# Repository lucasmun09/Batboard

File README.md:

# Batboard
Sonar amplification board to be used in conjunction with Arduino Due

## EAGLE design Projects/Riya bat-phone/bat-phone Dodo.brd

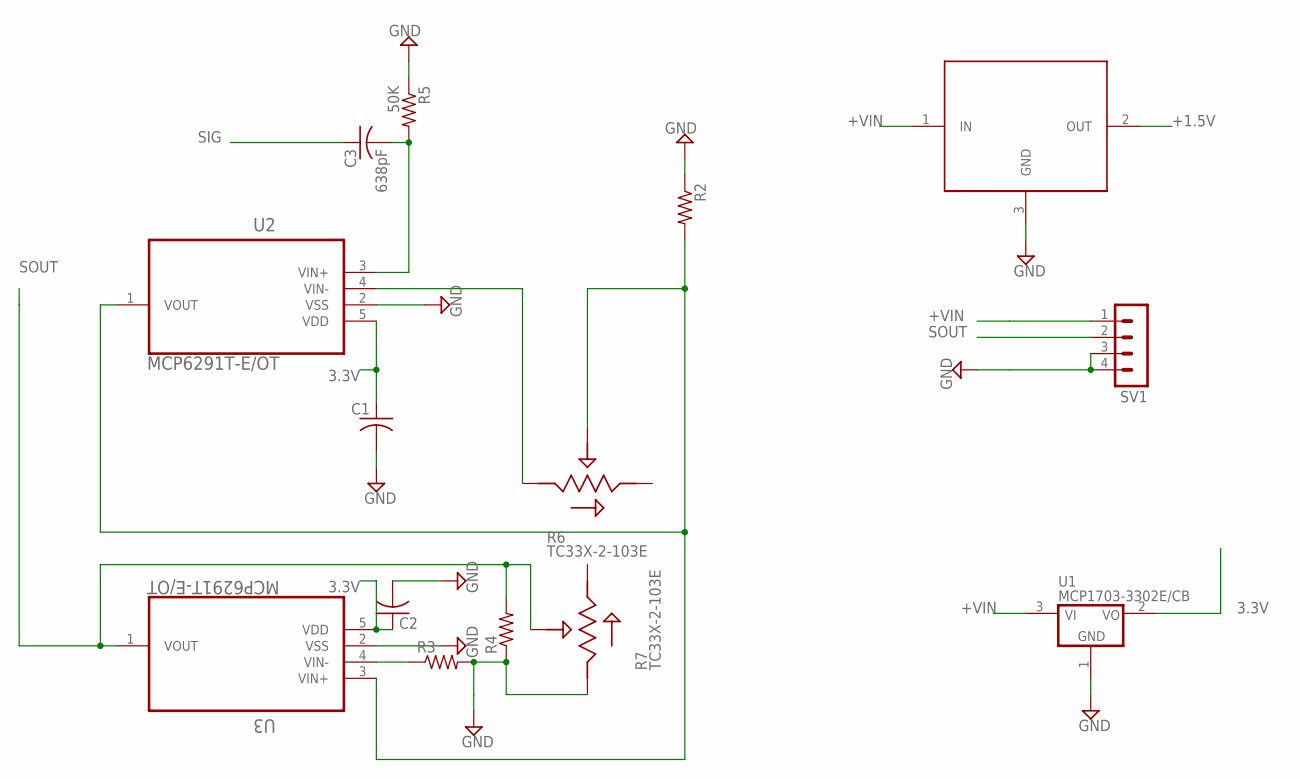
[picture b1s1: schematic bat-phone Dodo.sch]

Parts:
C1, C2: C-USC0603K; C0603K
C3: 638pF; C0603K
R2, R3, R4: R-US_R0603; R0603
R5: 50K; R0603
R6, R7: TC33X-2-103E; 35WR
SV1: MA04-1
U1: MCP1703-3302E/CB; SOT23A_MICROCHIP_CB
U2, U3: MCP6291T-E/OT; SOT95P320X145-5N
U$1: AP7313; SOT23-R

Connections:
3.3V: C1.1, C2.1, U1.2 (VO), U2.5 (VDD), U3.5 (VDD)
+1.5V: U$1.2 (OUT)
+VIN: SV1.1, U1.3 (VI), U$1.1 (IN)
GND: C1.2, C2.2, R2.1, R3.2, R4.1, R5.1, R7.1, SV1.3, SV1.4, U1.1 (GND), U2.2 (VSS), U3.2 (VSS), U$1.3 (GND)
unnamed: R6.1, U2.4 (VIN-)
unnamed: R2.2, R6.2, U2.1 (VOUT), U3.3 (VIN+)
unnamed: R3.1, U3.4 (VIN-)
unnamed: C3.2, R5.2, U2.3 (VIN+)
SIG: C3.1
SOUT: R4.2, R7.2, SV1.2, U3.1 (VOUT)

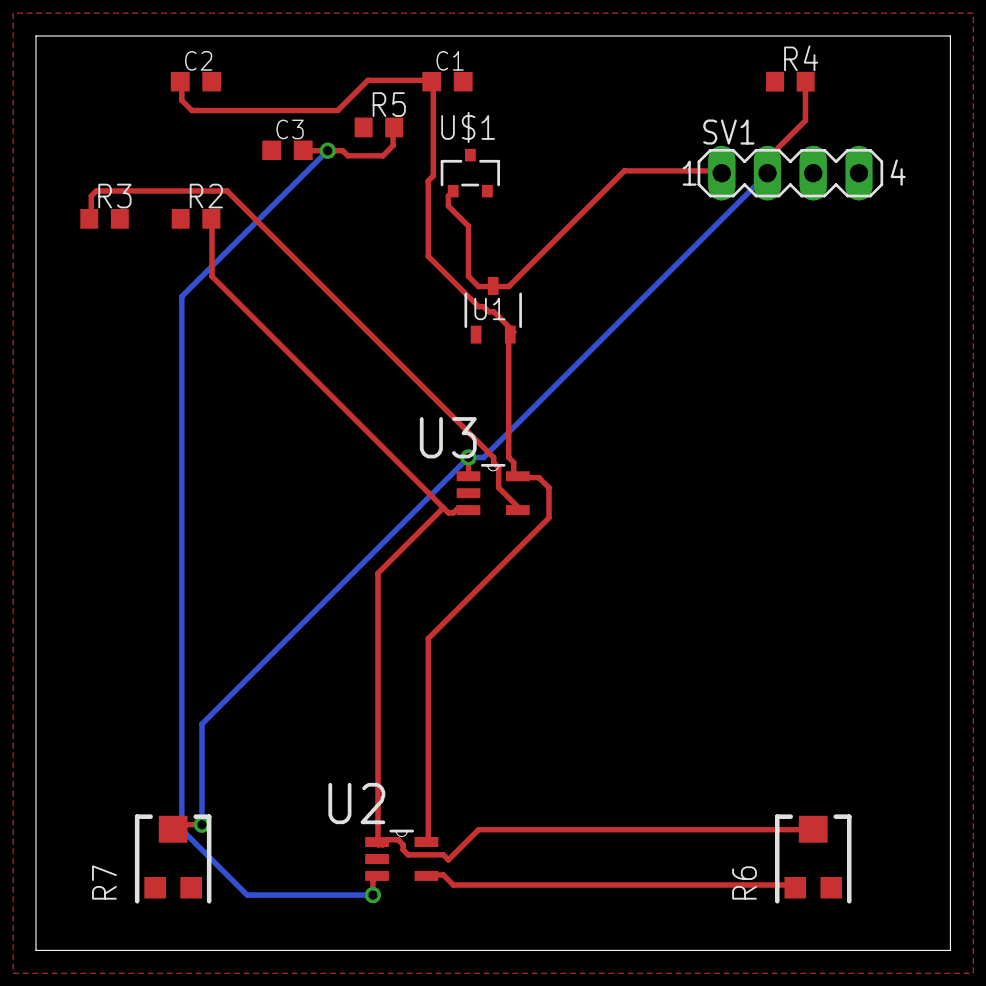
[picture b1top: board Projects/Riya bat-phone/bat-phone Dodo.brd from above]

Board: 2 copper layers, 50.8 x 50.8 mm, 14 parts (0 on the bottom side), 8 nets.

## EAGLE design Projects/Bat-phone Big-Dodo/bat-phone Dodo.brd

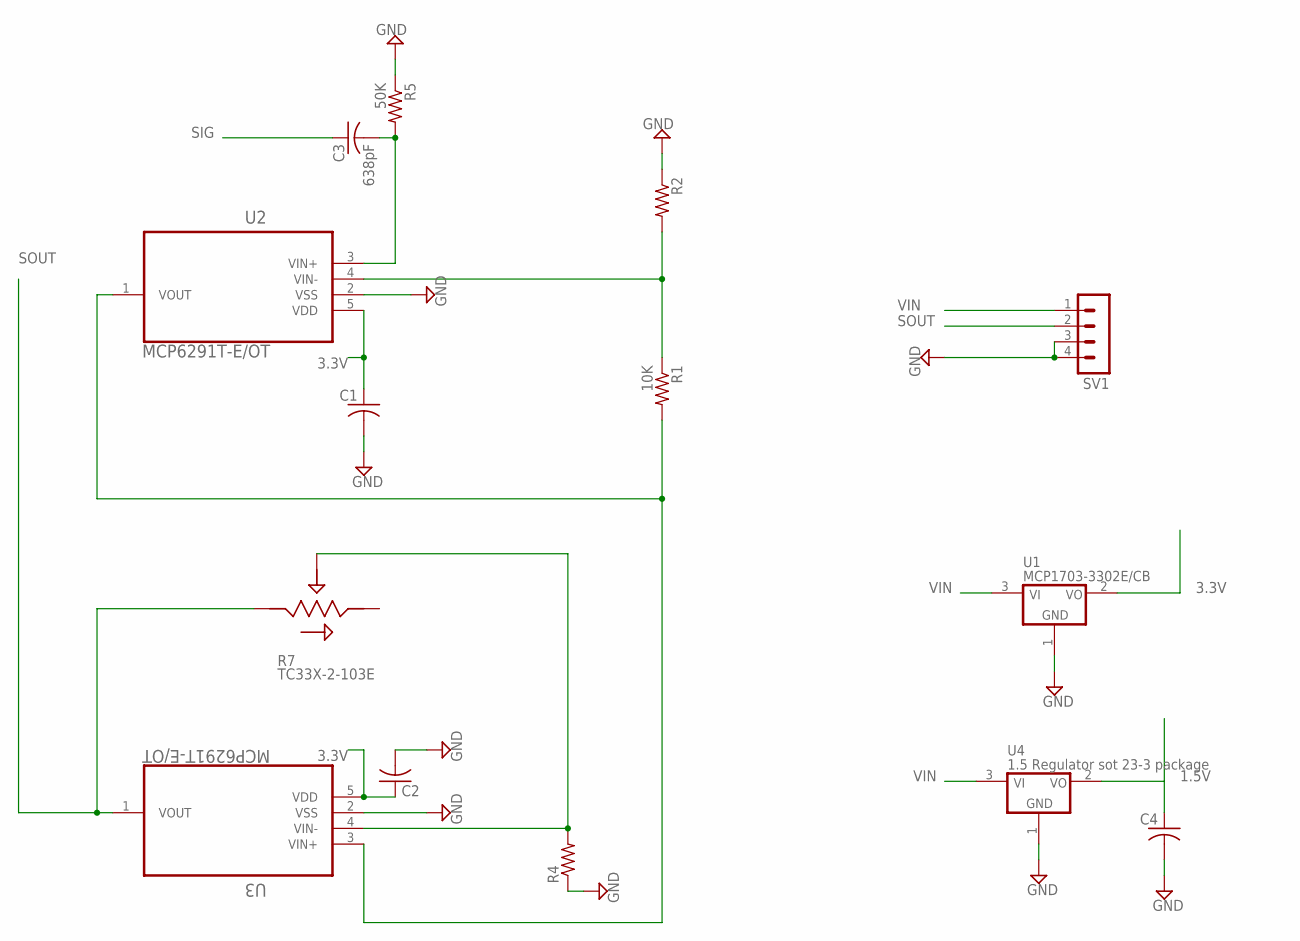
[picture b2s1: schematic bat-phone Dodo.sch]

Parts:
C1, C2, C4: C-USC0603K; C0603K
C3: 638pF; C0603K
R1: 10K; R0603
R2, R4: R-US_R0603; R0603
R5: 50K; R0603
R7: TC33X-2-103E; 35WR
SV1: MA04-1
U1: MCP1703-3302E/CB; SOT23A_MICROCHIP_CB
U2, U3: MCP6291T-E/OT; SOT95P320X145-5N
U4: 1.5 Regulator sot 23-3 package; SOT23A_MICROCHIP_CB

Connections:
1.5V: C4.1, U4.2 (VO)
3.3V: C1.1, C2.1, U1.2 (VO), U2.5 (VDD), U3.5 (VDD)
GND: C1.2, C2.2, C4.2, R2.1, R4.1, R5.1, SV1.3, SV1.4, U1.1 (GND), U2.2 (VSS), U3.2 (VSS), U4.1 (GND)
unnamed: R1.2, U2.1 (VOUT), U3.3 (VIN+)
unnamed: R1.1, R2.2, U2.4 (VIN-)
unnamed: R4.2, R7.2, U3.4 (VIN-)
unnamed: C3.2, R5.2, U2.3 (VIN+)
SIG: C3.1
SOUT: R7.1, SV1.2, U3.1 (VOUT)
VIN: SV1.1, U1.3 (VI), U4.3 (VI)

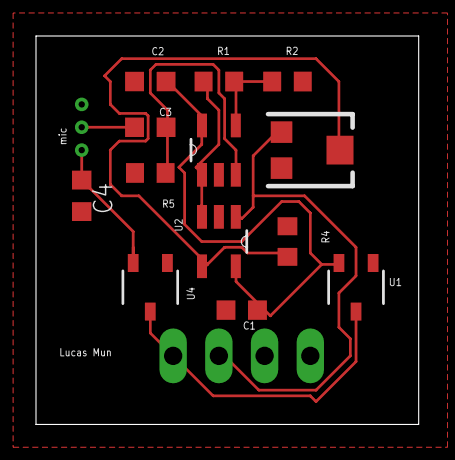
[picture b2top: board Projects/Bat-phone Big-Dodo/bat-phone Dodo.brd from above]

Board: 2 copper layers, 21.3 x 21.6 mm, 14 parts (1 on the bottom side), 9 nets.

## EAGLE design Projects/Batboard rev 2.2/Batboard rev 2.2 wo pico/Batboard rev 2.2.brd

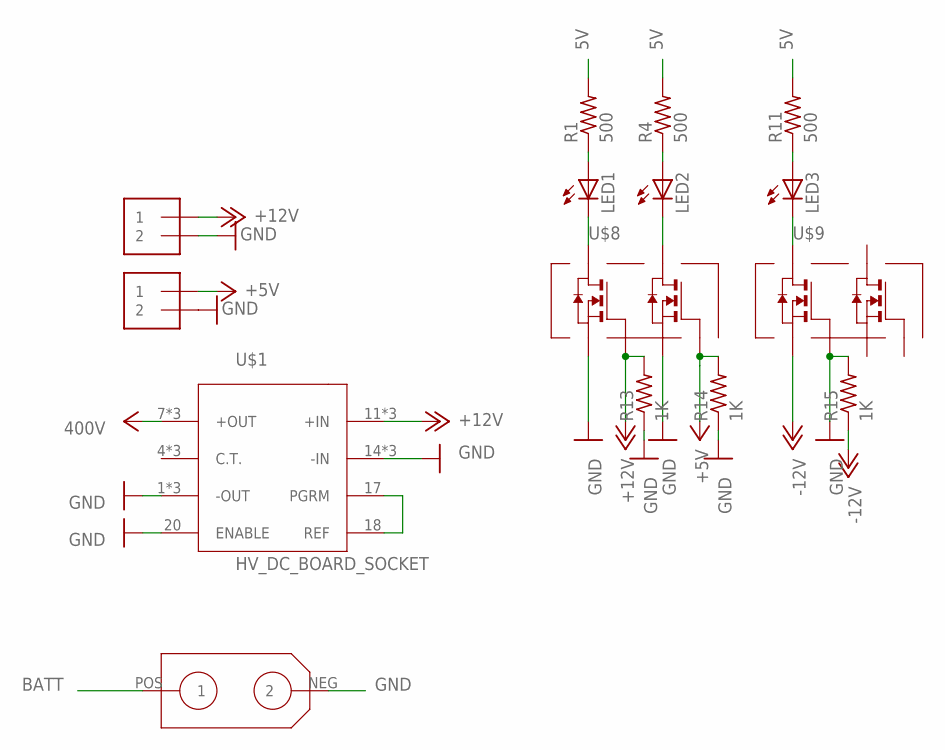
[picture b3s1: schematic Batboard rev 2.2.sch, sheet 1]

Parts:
J1, J6: 1X2-3.5MM
LED1, LED2, LED3: LED_E; LED_1206
R1, R4, R11: 500; R1206
R13, R14, R15: 1K; R1206
U$1: HV_DC_BOARD_SOCKET; HV-DC_BOARD_SOCKET
U$6: XT60
U$8, U$9: DMN2004DMK_DUAL_N-CHANNEL_MOSFET_ARRAY; SOT23-6

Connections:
5V: R1.2, R4.2, R11.2
+5V: J6.1, R14.2, U$8.2 (G1); also elsewhere on the board
+12V: J1.1, R13.2, U$1.11 (+IN), U$1.12 (+IN), U$1.13 (+IN), U$8.5 (G); also elsewhere on the board
-12V: R15.1, U$9.4 (S); also elsewhere on the board
BATT: U$6.POS (1); also elsewhere on the board
GND: J1.2, J6.2, R13.1, R14.1, R15.2, U$1.1 (-OUT), U$1.2 (-OUT), U$1.3 (-OUT), U$1.14 (-IN), U$1.15 (-IN), U$1.16 (-IN), U$1.20 (ENABLE), U$6.NEG (2), U$8.1 (S1), U$8.4 (S), U$9.5 (G); also elsewhere on the board
unnamed: U$1.17 (PGRM), U$1.18 (REF)
unnamed: LED1.A, R1.1
unnamed: LED2.A, R4.1
unnamed: LED3.A, R11.1
unnamed: LED3.C, U$9.6 (D)
unnamed: LED1.C, U$8.6 (D)
unnamed: LED2.C, U$8.3 (D1)
V+: U$1.7 (+OUT), U$1.8 (+OUT), U$1.9 (+OUT); also elsewhere on the board

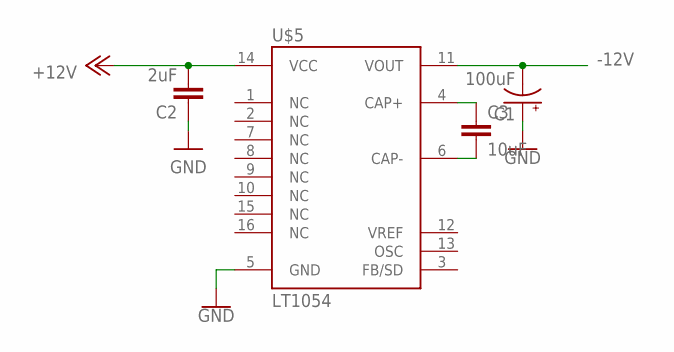
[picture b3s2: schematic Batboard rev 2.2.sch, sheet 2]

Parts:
C1: 100uF; PANASONIC_D
C2: 2uF; 1206; MPN C0805C103K1RACTU
C3: 10uF; 1206; MPN C0805C103K1RACTU
U$5: LT1054; SO16L

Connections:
+12V: C2.2, U$5.14 (VCC); also elsewhere on the board
-12V: C1.-, U$5.11 (VOUT); also elsewhere on the board
GND: C1.+, C2.1, U$5.5 (GND); also elsewhere on the board
unnamed: C3.1, U$5.4 (CAP+)
unnamed: C3.2, U$5.6 (CAP-)

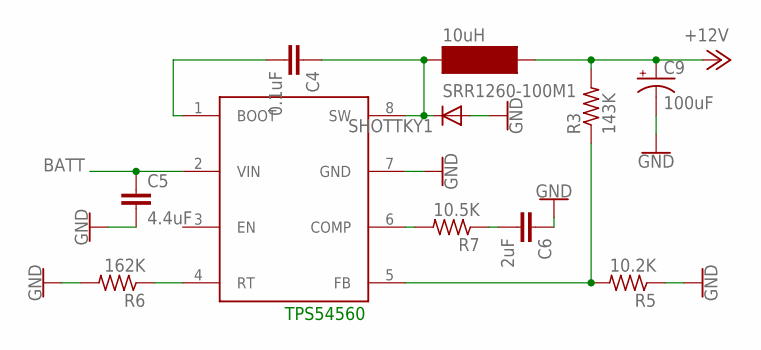
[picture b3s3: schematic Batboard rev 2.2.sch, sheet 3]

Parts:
C4: 0.1uF; 1206; MPN C0805C103K1RACTU
C5: 4.4uF; 1206; MPN C0805C103K1RACTU
C6: 2uF; 1206; MPN C0805C103K1RACTU
C9: 100uF; PANASONIC_D
R3: 143K; M1206; MPN WCR0805-18KFI
R5: 10.2K; M1206; MPN WCR0805-18KFI
R6: 162K; M1206; MPN WCR0805-18KFI
R7: 10.5K; M1206; MPN WCR0805-18KFI
SHOTTKY1: DIODE-DO214AC; DO214AC
SRR1260-100M1: 10uH; 12.5*12.5
TPS1: TPS54560; SOIC127P600X175-8N

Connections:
+12V: C9.+, R3.2, SRR1260-100M1.P$2; also elsewhere on the board
BATT: C5.1, TPS1.2 (VIN); also elsewhere on the board
GND: C5.2, C6.1, C9.-, R5.1, R6.2, SHOTTKY1.A, TPS1.7 (GND); also elsewhere on the board
unnamed: C4.2, TPS1.1 (BOOT)
unnamed: C4.1, SHOTTKY1.C, SRR1260-100M1.P$1, TPS1.8 (SW)
unnamed: R3.1, R5.2, TPS1.5 (FB)
unnamed: R6.1, TPS1.4 (RT)
unnamed: R7.2, TPS1.6 (COMP)
unnamed: C6.2, R7.1

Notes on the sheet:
TPS54560

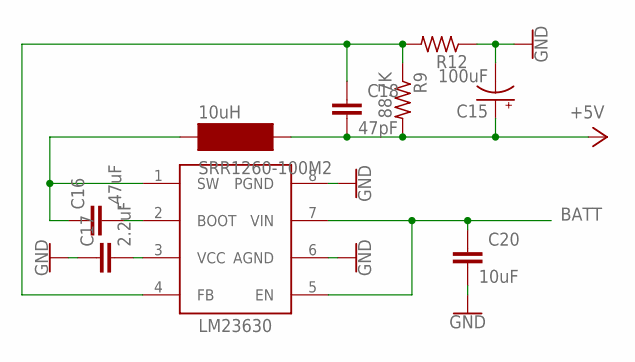
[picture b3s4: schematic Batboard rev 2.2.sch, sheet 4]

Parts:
C15: 100uF; PANASONIC_D
C16: .47uF; 1206; MPN C0805C103K1RACTU
C17: 2.2uF; 1206; MPN C0805C103K1RACTU
C18: 47pF; 1206; MPN C0805C103K1RACTU
C20: 10uF; 1206; MPN C0805C103K1RACTU
R9: 88.7K; M1206; MPN WCR0805-18KFI
R12: 22.1K; M1206; MPN WCR0805-18KFI
SRR1260-100M2: 10uH; 12.5*12.5
U$7: LM23630; SOIC127P602X168-8N

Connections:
+5V: C15.+, C18.2, R9.2, SRR1260-100M2.P$2; also elsewhere on the board
BATT: C20.1, U$7.5 (EN), U$7.7 (VIN); also elsewhere on the board
GND: C15.-, C17.1, C20.2, R12.1, U$7.6 (AGND), U$7.8 (PGND); also elsewhere on the board
unnamed: C16.2, U$7.2 (BOOT)
unnamed: C16.1, SRR1260-100M2.P$1, U$7.1 (SW)
unnamed: C18.1, R9.1, R12.2, U$7.4 (FB)
unnamed: C17.2, U$7.3 (VCC)

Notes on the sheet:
LM23630

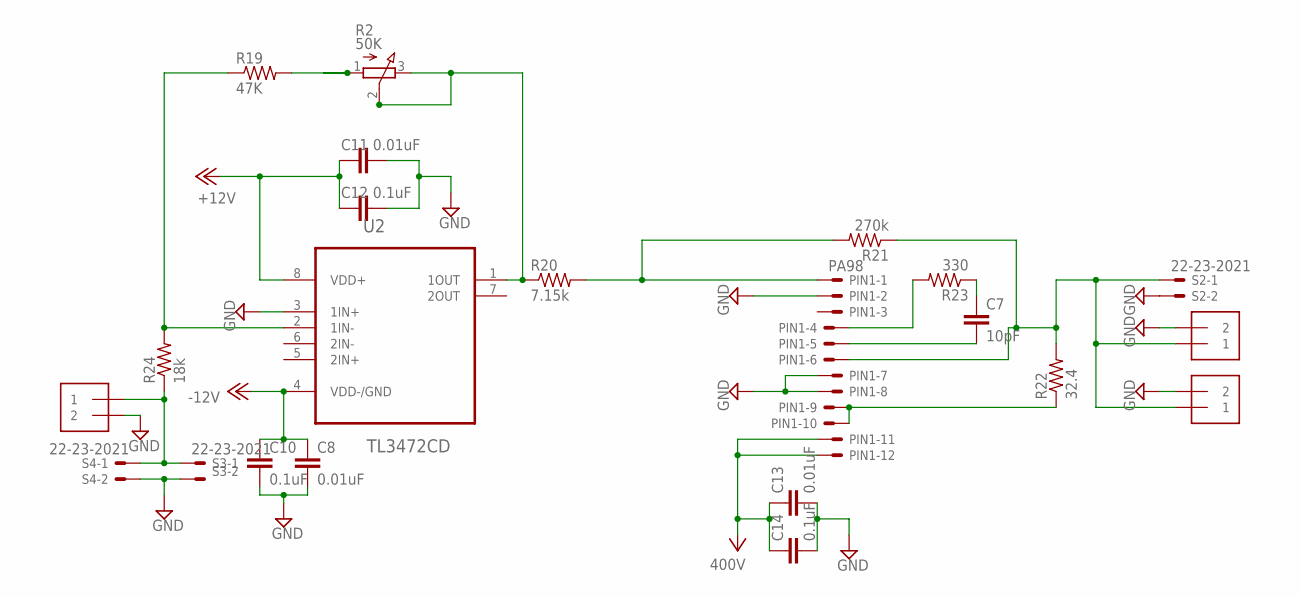
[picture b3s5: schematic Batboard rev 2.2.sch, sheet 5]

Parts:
C7: 10pF; 1206; MPN C0805C479C5GACTU
C8, C11, C13: 0.01uF; 1206; MPN C0805C103K1RACTU
C10, C12, C14: 0.1uF; 1206; MPN C0805C104J5RACTU
J2, J3, J5: 1X2-3.5MM
PIN1: PA98; 22-23-2121
R2: 50K; 3RP/1610N
R19: 47K; M1206; MPN SG73S2ATTD9102F
R20: 7.15k; M1206; MPN CRCW08057K15FKEA
R21: 270k; M1206; MPN WCR0805-270KFI
R22: 32.4; M1206; MPN ERJ8ENF32R4V
R23: 330; M1206; MPN ERJ8ENF32R4V
R24: 18k; M1206; MPN WCR0805-18KFI
S2, S3, S4: 22-23-2021
U2: TL3472CD; SOIC127P600X175-8N

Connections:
+12V: C11.1, C12.1, U2.8 (VDD+); also elsewhere on the board
-12V: C8.1, C10.1, U2.4 (VDD-/GND); also elsewhere on the board
GND: C8.2, C10.2, C11.2, C12.2, C13.2, C14.2, J2.2, J3.2, J5.2, PIN1.2, PIN1.7, PIN1.8, S2.2, S3.2, S4.2, U2.3 (1IN+); also elsewhere on the board
unnamed: J5.1, R24.1, S3.1, S4.1
unnamed: R19.1, R24.2, U2.2 (1IN-)
unnamed: R2.2 (S), R2.3 (E), R20.1, U2.1 (1OUT)
unnamed: PIN1.1, R20.2, R21.2
unnamed: PIN1.9, PIN1.10, R22.1
unnamed: PIN1.4, R23.2
unnamed: J2.1, J3.1, PIN1.6, R21.1, R22.2, S2.1
unnamed: R2.1 (A), R19.2
unnamed: C7.2, PIN1.5
unnamed: C7.1, R23.1
V+: C13.1, C14.1, PIN1.11, PIN1.12; also elsewhere on the board

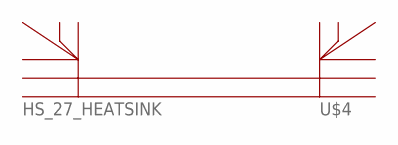
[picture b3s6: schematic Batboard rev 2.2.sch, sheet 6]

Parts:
U$4: HS_27_HEATSINK

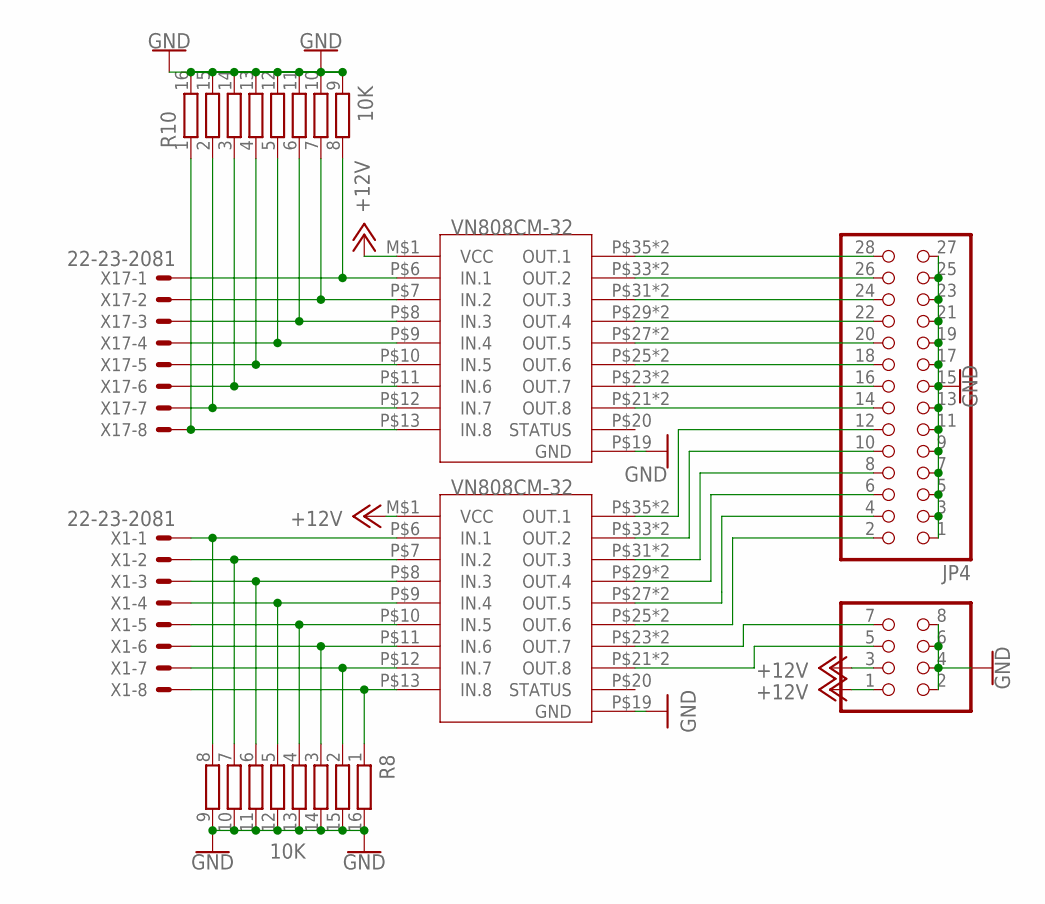
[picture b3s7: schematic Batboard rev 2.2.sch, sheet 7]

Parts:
JP3: PINHD-2X4; 2X04
JP4: PINHD-2X14-CB; 2X14-CLEANBIG
R8, R10: 10K; 4816P
U$2, U$3: VN808CM-32-E; PSO36
X1, X17: 22-23-2081

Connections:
+12V: JP3.1, JP3.3, U$2.M$1 (VCC), U$3.M$1 (VCC); also elsewhere on the board
GND: JP3.2, JP3.4, JP3.6, JP3.8, JP4.1, JP4.3, JP4.5, JP4.7, JP4.9, JP4.11, JP4.13, JP4.15, JP4.17, JP4.19, JP4.21, JP4.23, JP4.25, JP4.27, R8.9, R8.10, R8.11, R8.12, R8.13, R8.14, R8.15, R8.16, R10.9, R10.10, R10.11, R10.12, R10.13, R10.14, R10.15, R10.16, U$2.P$19 (GND), U$3.P$19 (GND); also elsewhere on the board
unnamed: R10.8, U$2.P$6 (IN.1), X17.1
unnamed: R10.7, U$2.P$7 (IN.2), X17.2
unnamed: JP4.28, U$2.P$35 (OUT.1), U$2.P$36 (OUT.1)
unnamed: JP4.26, U$2.P$33 (OUT.2), U$2.P$34 (OUT.2)
unnamed: JP4.24, U$2.P$31 (OUT.3), U$2.P$32 (OUT.3)
unnamed: JP4.22, U$2.P$29 (OUT.4), U$2.P$30 (OUT.4)
unnamed: JP4.20, U$2.P$27 (OUT.5), U$2.P$28 (OUT.5)
unnamed: JP4.18, U$2.P$25 (OUT.6), U$2.P$26 (OUT.6)
unnamed: JP4.16, U$2.P$23 (OUT.7), U$2.P$24 (OUT.7)
unnamed: JP4.14, U$2.P$21 (OUT.8), U$2.P$22 (OUT.8)
unnamed: JP4.12, U$3.P$35 (OUT.1), U$3.P$36 (OUT.1)
unnamed: JP4.10, U$3.P$33 (OUT.2), U$3.P$34 (OUT.2)
unnamed: JP4.8, U$3.P$31 (OUT.3), U$3.P$32 (OUT.3)
unnamed: JP4.6, U$3.P$29 (OUT.4), U$3.P$30 (OUT.4)
unnamed: JP4.4, U$3.P$27 (OUT.5), U$3.P$28 (OUT.5)
unnamed: JP4.2, U$3.P$25 (OUT.6), U$3.P$26 (OUT.6)
unnamed: JP3.7, U$3.P$23 (OUT.7), U$3.P$24 (OUT.7)
unnamed: JP3.5, U$3.P$21 (OUT.8), U$3.P$22 (OUT.8)
unnamed: R8.8, U$3.P$6 (IN.1), X1.1
unnamed: R10.1, U$2.P$13 (IN.8), X17.8
unnamed: R10.2, U$2.P$12 (IN.7), X17.7
unnamed: R10.6, U$2.P$8 (IN.3), X17.3
unnamed: R10.3, U$2.P$11 (IN.6), X17.6
unnamed: R10.4, U$2.P$10 (IN.5), X17.5
unnamed: R10.5, U$2.P$9 (IN.4), X17.4
unnamed: R8.1, U$3.P$13 (IN.8), X1.8
unnamed: R8.2, U$3.P$12 (IN.7), X1.7
unnamed: R8.7, U$3.P$7 (IN.2), X1.2
unnamed: R8.6, U$3.P$8 (IN.3), X1.3
unnamed: R8.3, U$3.P$11 (IN.6), X1.6
unnamed: R8.4, U$3.P$10 (IN.5), X1.5
unnamed: R8.5, U$3.P$9 (IN.4), X1.4

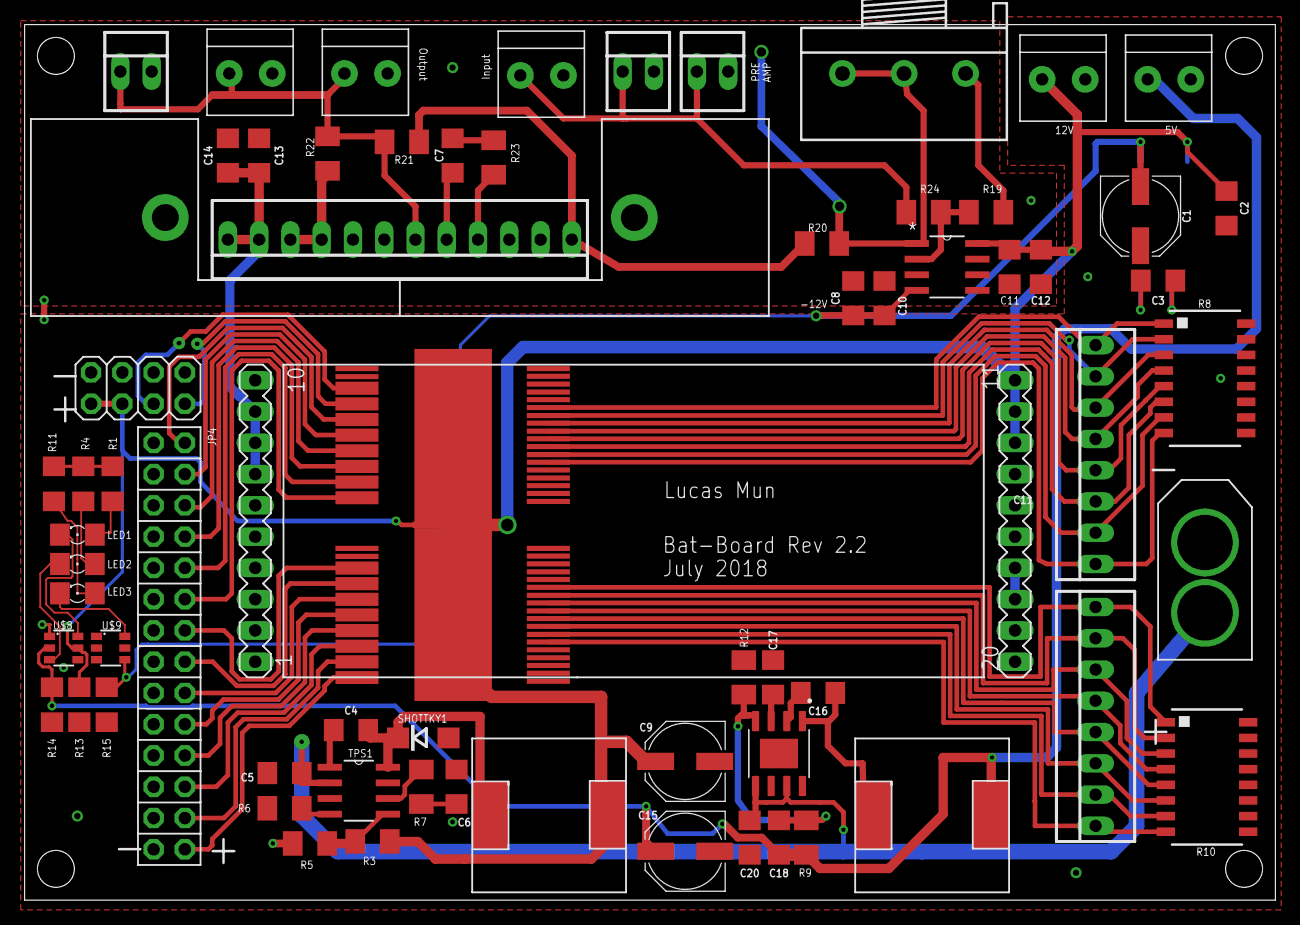
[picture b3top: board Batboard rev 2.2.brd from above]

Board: 2 copper layers, 101.6 x 71.1 mm, 70 parts (1 on the bottom side), 68 nets.

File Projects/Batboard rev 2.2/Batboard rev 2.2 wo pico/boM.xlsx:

Part | Value | Device | Package | Description | MIN RATING | Link
C1 | 100uF | 100UF-POLAR-25V-20%(ELEC) | PANASONIC_D | smd polarized capacitor | 15V | https://www.mouser.com/ProductDetail/TDK/C3216X8L1H225K160AC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
C2 | 2uF | 1.0UF-1206-50V-10% | 1206 | CERAMIC | 15V | https://www.mouser.com/ProductDetail/Wurth-Electronics/88501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
C3 | 10uF | 1.0UF-1206-50V-10% | 1206 | CERAMIC | 15V | https://www.mouser.com/ProductDetail/Vishay-Vitramon/VJ1206Y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
C4 | 0.1uF | 1.0UF-1206-50V-10% | 1206 | CERAMIC | 15V | https://www.mouser.com/ProductDetail/Vishay-Vitramon/VJ1206Y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
C5 | 4.4uF | 1.0UF-1206-50V-10% | 1206 | CERAMIC | 15V | https://www.mouser.com/ProductDetail/Murata-Electronics/GCG3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
C6 | 2uF | 1.0UF-1206-50V-10% | 1206 | CERAMIC | 15V | C2
C7 | 10pF | 1.0UF-1206-50V-10% | 1206 | CERAMIC | 450V | https://www.mouser.com/ProductDetail/Yageo/CC1206JRNPOBBN100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
C8 | 0.01uF | 1.0UF-1206-50V-10% | 1206 | CERAMIC | 15V | https://www.mouser.com/ProductDetail/Vishay-Vitramon/VJ1206Y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
C9 | 100uF | 1.0UF-1206-50V-10% | 1206 | smd polarized capacitor | 15V | C1
C10 | 0.1uF | 1.0UF-1206-50V-10% | 1206 | CERAMIC | 15V | C4
C11 | 0.01uF | 1.0UF-1206-50V-10% | 1206 | CERAMIC | 15V | C8
C12 | 0.1uF | 1.0UF-1206-50V-10% | 1206 | CERAMIC | 15V | C4
C13 | 0.01uF | 1.0UF-1206-50V-10% | 1206 | CERAMIC | 450V | C8
C14 | 0.1uF | 1.0UF-1206-50V-10% | 1206 | CERAMIC | 450V | C4
C16 | .47uF | 1.0UF-1206-50V-10% | 1206 | CERAMIC | 15V | https://www.mouser.com/ProductDetail/Vishay-Vitramon/VJ1206Y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
C17 | 2.2uF | 1.0UF-1206-50V-10% | 1206 | CERAMIC | 15V | C2
C18 | 47pF | 1.0UF-1206-50V-10% | 1206 | CERAMIC | 15V | https://www.mouser.com/ProductDetail/Vishay-Vitramon/VJ1206A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
C20 | 10uF | 1.0UF-1206-50V-10% | 1206 | CERAMIC | 15V | C3
C21 | 100uF | 1.0UF-1206-50V-10% | 1206 | smd polarized capacitor | 15V | C1
J1 | 1X2-3.5MM | 1X2-3.5MM | 1X2-3.5MM | 3.5mm Terminal block |  | https://www.digikey.com/product-detail/en/te-connectivity-am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
J2 | 1X2-3.5MM | 1X2-3.5MM | 1X2-3.5MM | 3.5mm Terminal block |  | Check J1
J3 | 1X2-3.5MM | 1X2-3.5MM | 1X2-3.5MM | 3.5mm Terminal block |  | Check J1
J4 | 1X2-3.5MM | 1X2-3.5MM | 1X2-3.5MM | 3.5mm Terminal block |  | Check J1
J5 | 1X2-3.5MM | 1X2-3.5MM | 1X2-3.5MM | 3.5mm Terminal block |  | Check J1
J6 | 1X2-3.5MM | 1X2-3.5MM | 1X2-3.5MM | 3.5mm Terminal block |  | Check J1
JP3 | 2.54 MM | PINHD-2X4 | 2X04 | SECONDARY VALVE HEADER |  | Typical 2.54mm male pins
JP4 | 2.54 MM | PINHD-2X14-CB | 2X14-CLEANBIG | MAIN VALVE HEADER |  | Typical 2.54mm male pins
LED1 | RED | LED_E | LED_1206 | indicator led
LED2 | RED | LED_E | LED_1206 | indicator led
LED3 | RED | LED_E | LED_1206 | indicator led
PIN1 | PA98 | 22-23-2121 | 22-23-2121 | MAIN AMPLIFIER |  | https://www.digikey.com/product-detail/en/apex-microtechnolo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
R1 | 500 | R-US_R1206 | R1206 | RESISTOR, American symbol |  | https://www.mouser.com/ProductDetail/Yageo/RT1206FRE07499RL?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
R2 | 50K | 3RP/1610N | 3RP/1610N | 16mm Potentiometer one level | LINEAR | https://www.amazon.com/Uxcell-a15040700ux0370-Terminal-Linea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
R3 | 143K | R-US_M1206 | M1206 | RESISTOR, American symbol |  | https://www.mouser.com/ProductDetail/TE-Connectivity-Neohm/C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
R4 | 500 | R-US_R1206 | R1206 | RESISTOR, American symbol |  | https://www.mouser.com/ProductDetail/Yageo/RT1206FRE07499RL?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
R5 | 10.2K | R-US_M1206 | M1206 | RESISTOR, American symbol
R6 | 162K | R-US_M1206 | M1206 | RESISTOR, American symbol
R7 | 10.5K | R-US_M1206 | M1206 | RESISTOR, American symbol
R8 | 10K | 4816P-T01 | 4816P | BOURNS RESISTOR NETWORK
R9 | 88.7K | R-US_M1206 | M1206 | RESISTOR, American symbol
R10 | 10K | 4816P-T01 | 4816P | BOURNS RESISTOR NETWORK
R11 | 500 | R-US_R1206 | R1206 | RESISTOR, American symbol
R12 | 22.1K | R-US_M1206 | M1206 | RESISTOR, American symbol
R13 | 1K | R-US_R1206 | R1206 | RESISTOR, American symbol
R14 | 1K | R-US_R1206 | R1206 | RESISTOR, American symbol
R15 | 1K | R-US_R1206 | R1206 | RESISTOR, American symbol
R19 | 47K | R-US_M1206 | M1206 | RESISTOR, American symbol
R20 | 7.15k | R-US_M1206 | M1206 | RESISTOR, American symbol
R21 | 270k | R-US_M1206 | M1206 | RESISTOR, American symbol
R22 | 32.4 | R-US_M1206 | M1206 | RESISTOR, American symbol
R23 | 330 | R-US_M1206 | M1206 | RESISTOR, American symbol
R24 | 18k | R-US_M1206 | M1206 | RESISTOR, American symbol
S1 | 2.54 MM | 22-23-2021 | 22-23-2021 | .100" (2.54mm) Center Header - 2 Pin
S2 | 2.54 MM | 22-23-2021 | 22-23-2021 | .100" (2.54mm) Center Header - 2 Pin
S3 | 2.54 MM | 22-23-2021 | 22-23-2021 | .100" (2.54mm) Center Header - 2 Pin
S4 | 2.54 MM | 22-23-2021 | 22-23-2021 | .100" (2.54mm) Center Header - 2 Pin
SHOTTKY1 |  | DIODE-DO214AC | DO214AC | DIODE
SLF1 | 10uH | SLF10165 | 10.1*10.1
SRR1260-100M1 | 10uH | SRR1260-100M | 12.5*12.5
TPS1 | TPS54560(8) | TPS54560(8) | SOIC127P600X175-8N
U$1 | HV_DC_BOARD_SOCKET | HV_DC_BOARD_SOCKET | HV-DC_BOARD_SOCKET
U$2 | VN808CM-32-E | VN808CM-32-E | PSO36
U$3 | VN808CM-32-E | VN808CM-32-E | PSO36
U$4 | HS_27_HEATSINK | HS_27_HEATSINK | HS_27_HEATSINK
U$5 | LT1054 | LT1054 | SO16L | The LT1054 is a bipolar, switched-capacitor voltage converter with regulator.
U$6 | XT60 | XT60 | XT60
U$7 | LM23630 | LM23630 | SOIC127P602X168-8N | LM23630 5V 3A
U$8 | DMN2004DMK_DUAL_N-CHANNEL_MOSFET_ARRAY | DMN2004DMK_DUAL_N-CHANNEL_MOSFET_ARRAY | SOT23-6
U$9 | DMN2004DMK_DUAL_N-CHANNEL_MOSFET_ARRAY | DMN2004DMK_DUAL_N-CHANNEL_MOSFET_ARRAY | SOT23-6
U2 | TL3472CD | TL3472CD | SOIC127P600X175-8N | HIGH-SLEW-RATE, SINGLE-SUPPLY OPERATIONAL AMPLIFIER
X1 | 22-23-2081 | 22-23-2081 | 22-23-2081 | .100" (2.54mm) Center Header - 8 Pin
X17 | 22-23-2081 | 22-23-2081 | 22-23-2081 | .100" (2.54mm) Center Header - 8 Pin

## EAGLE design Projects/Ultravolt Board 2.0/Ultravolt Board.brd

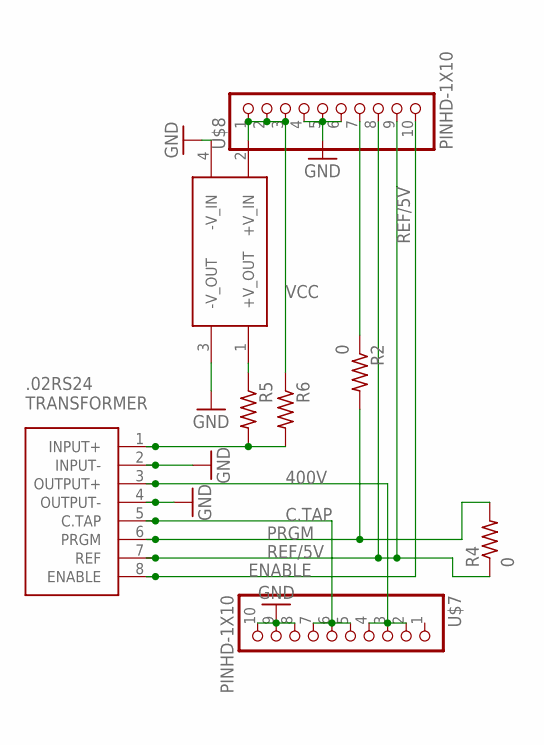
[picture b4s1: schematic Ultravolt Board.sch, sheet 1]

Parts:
$ZX2: LUCAS-LIBRARY_12_DC-24_DC
R2, R4: 0; M1206
R5, R6: ADAFRUIT_R-US_M0805; ADAFRUIT_M0805
U$1: ULTRAVOLT_DAUGHTERBOARD_BAT-BOARD-REV-2.0_LUCAS-L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; ULTRAVOLT_DAUGHTERBOARD_BAT-BOARD-REV-2.0_LUCAS-LIBRARY_0.2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
U$7, U$8: PINHD-1X10; 1X10-BIG

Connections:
24V: $ZX2.1 (+V_OUT), R5.1
400V: U$1.3 (OUTPUT+), U$7.2, U$7.3, U$7.4
C.TAP: U$1.5 (C.TAP), U$7.5, U$7.6, U$7.7
ENABLE: U$1.8 (ENABLE), U$8.10
GND: $ZX2.3 (-V_OUT), $ZX2.4 (-V_IN), U$1.2 (INPUT-), U$1.4 (OUTPUT-), U$7.8, U$7.9, U$7.10, U$8.4, U$8.5, U$8.6
unnamed: R2.1, U$8.7
unnamed: R5.2, R6.2, U$1.1 (INPUT+)
PRGM: R2.2, R4.2, U$1.6 (PRGM)
REF/5V: R4.1, U$1.7 (REF), U$8.8, U$8.9
VCC: $ZX2.2 (+V_IN), R6.1, U$8.1, U$8.2, U$8.3

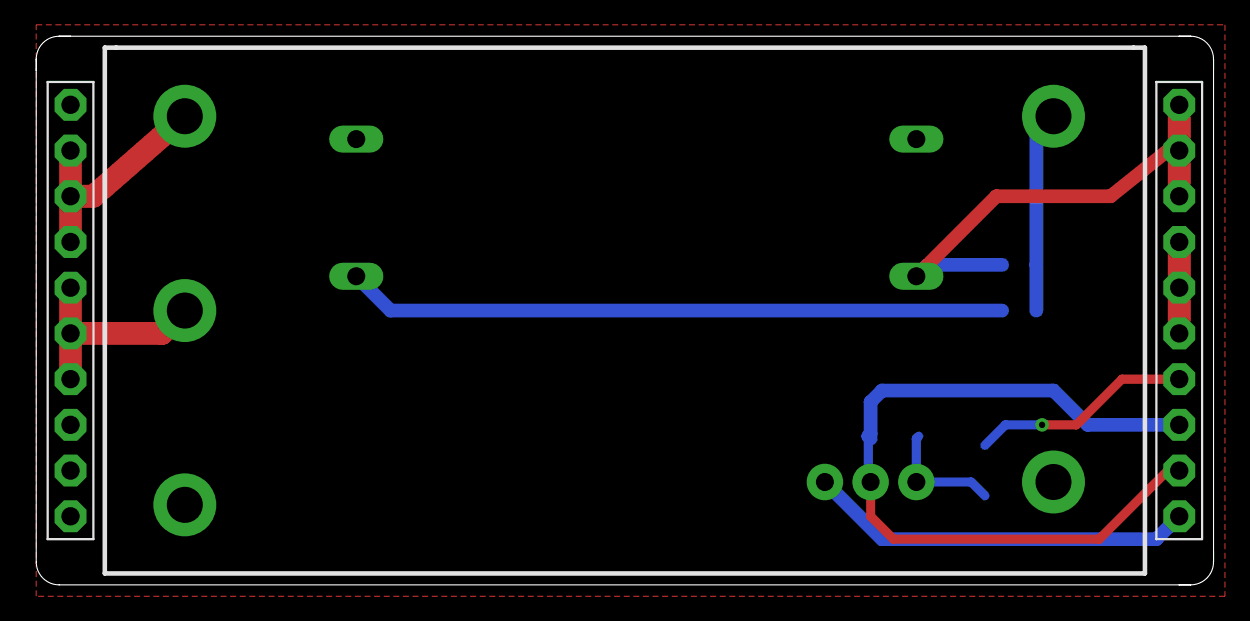
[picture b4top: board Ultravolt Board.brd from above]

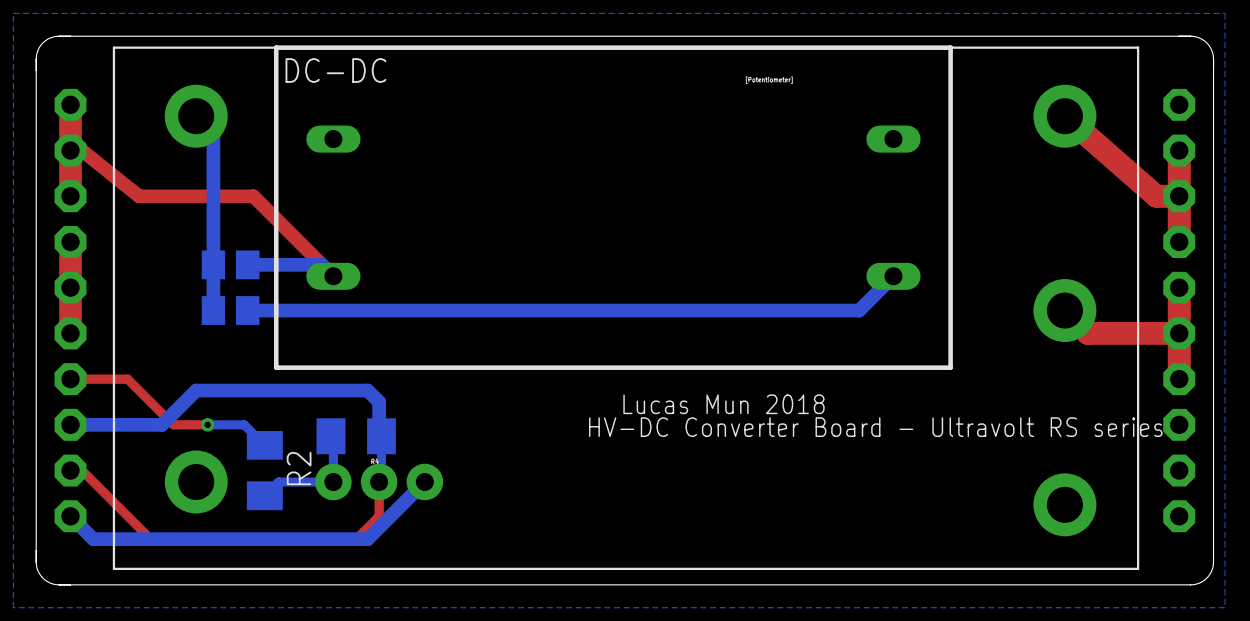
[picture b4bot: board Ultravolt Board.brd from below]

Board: 2 copper layers, 65.4 x 30.5 mm, 8 parts (5 on the bottom side), 10 nets.

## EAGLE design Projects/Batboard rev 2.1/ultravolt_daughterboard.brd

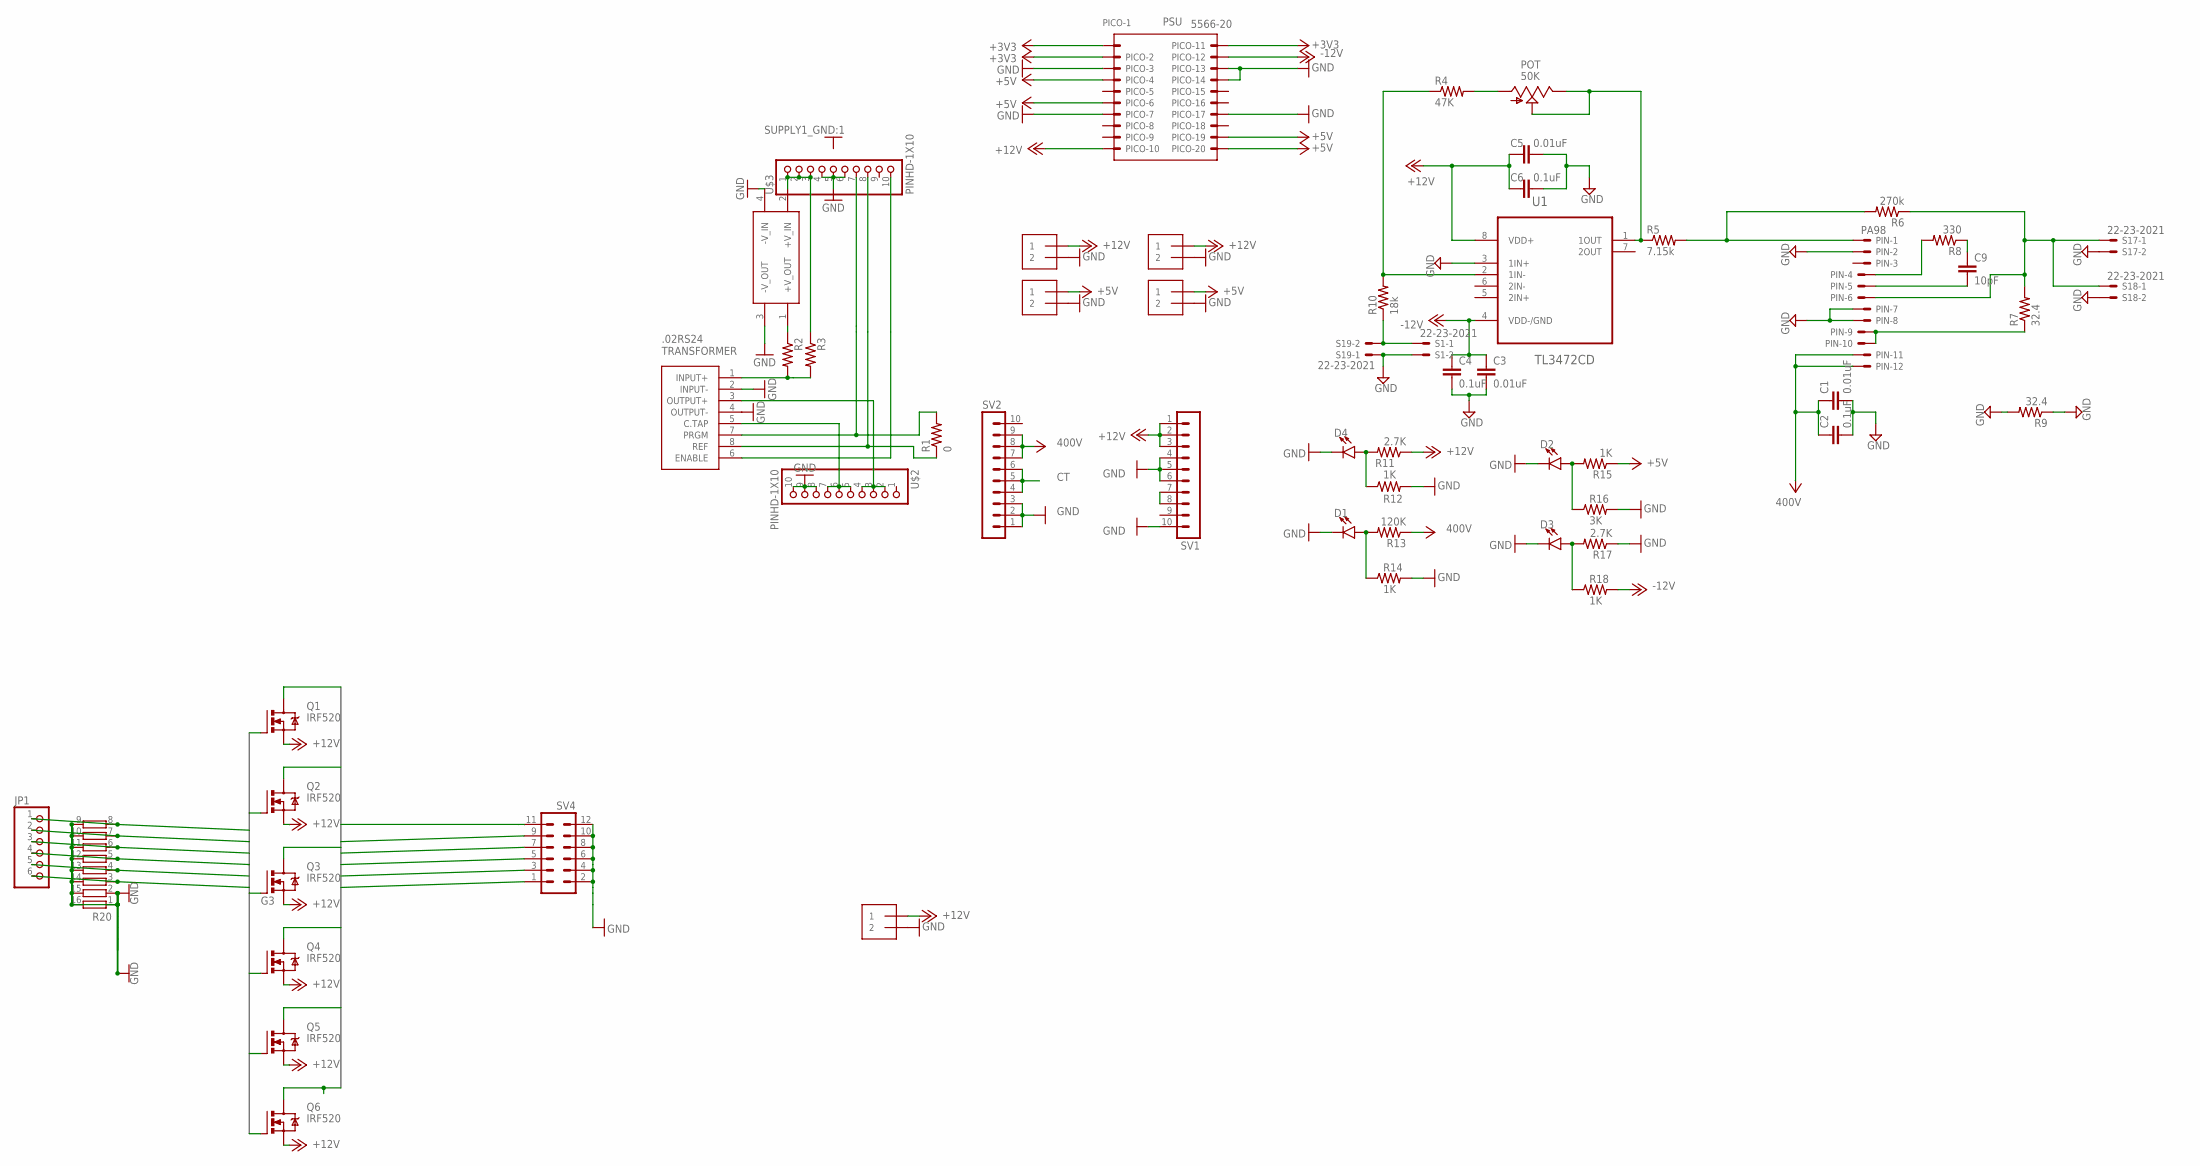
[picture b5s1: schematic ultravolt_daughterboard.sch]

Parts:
$ZX1: LUCAS-LIBRARY_12_DC-24_DC
C1, C3, C5: 0.01uF; 1206; MPN C0805C103K1RACTU
C2, C4, C6: 0.1uF; 1206; MPN C0805C104J5RACTU
C9: 10pF; 1206; MPN C0805C479C5GACTU
D1, D2, D3, D4: LED1206; LED-1206
J1, J2, J4, J6, J8: 1X2-3.5MM
JP1: PINHD-1X6; 1X06
PICO: 5566-20
PIN: PA98; 22-23-2121
POT: 50K; 3223W
Q1, Q2, Q3, Q4, Q5, Q6: IRF520; TO220BV
R1: 0; M1206
R2, R3: ADAFRUIT_R-US_M0805; ADAFRUIT_M0805
R4: 47K; M1206; MPN SG73S2ATTD9102F
R5: 7.15k; M1206; MPN CRCW08057K15FKEA
R6: 270k; M1206; MPN WCR0805-270KFI
R7, R9: 32.4; M1206; MPN ERJ8ENF32R4V
R8: 330; M1206; MPN ERJ8ENF32R4V
R10: 18k; M1206; MPN WCR0805-18KFI
R11, R17: 2.7K; M1206; MPN WCR0805-18KFI
R12, R14, R15, R18: 1K; M1206; MPN WCR0805-18KFI
R13: 120K; M1206; MPN WCR0805-18KFI
R16: 3K; M1206; MPN WCR0805-18KFI
R20: 4816P-T01; 4816P
S1, S17, S18, S19: 22-23-2021
SV1, SV2: MA10-1
SV4: MA06-2
U1: TL3472CD; SOIC127P600X175-8N
U$1: LUCAS-LIBRARY_.2RS24_TRANSFORMER; LUCAS-LIBRARY_0.2RS24_TRANSFORMER
U$2, U$3: PINHD-1X10; 1X10-BIG

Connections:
+3V3: PICO.1, PICO.2, PICO.11
+5V: J6.1, J8.1, PICO.4, PICO.6, PICO.19, PICO.20, R15.1
+12V: C5.1, C6.1, J1.1, J2.1, J4.1, PICO.10, Q1.S, Q2.S, Q3.S, Q4.S, Q5.S, Q6.S, R11.1, SV1.1, SV1.2, SV1.3, U1.8 (VDD+)
-12V: C3.1, C4.1, PICO.12, R18.2, U1.4 (VDD-/GND)
CT: SV2.4, SV2.5, SV2.6
D1: Q1.D, SV4.11
D2: Q2.D, SV4.9
D3: Q3.D, SV4.7
D4: Q4.D, SV4.5
D5: Q5.D, SV4.3
D6: Q6.D, SV4.1
G1: JP1.1, Q1.G, R20.8
G2: JP1.2, Q2.G, R20.7
G3: JP1.3, Q3.G, R20.6
G4: JP1.4, Q4.G, R20.5
G5: JP1.5, Q5.G, R20.4
G6: JP1.6, Q6.G, R20.3
GND: $ZX1.3 (-V_OUT), $ZX1.4 (-V_IN), C1.2, C2.2, C3.2, C4.2, C5.2, C6.2, D1.C, D2.C, D3.C, D4.C, J1.2, J2.2, J4.2, J6.2, J8.2, PICO.3, PICO.7, PICO.13, PICO.14, PICO.17, PIN.2, PIN.7, PIN.8, R9.1, R9.2, R12.2, R14.2, R16.2, R17.1, R20.1, R20.9, R20.10, R20.11, R20.12, R20.13, R20.14, R20.15, R20.16, S1.2, S17.2, S18.2, S19.1, SV1.4, SV1.5, SV1.6, SV1.10, SV2.1, SV2.2, SV2.3, SV4.2, SV4.4, SV4.6, SV4.8, SV4.10, SV4.12, U1.3 (1IN+), U$1.2 (INPUT-), U$1.4 (OUTPUT-), U$2.8, U$2.9, U$2.10, U$3.4, U$3.5, U$3.6
unnamed: $ZX1.2 (+V_IN), R3.1, U$3.1, U$3.2, U$3.3
unnamed: $ZX1.1 (+V_OUT), R2.1
unnamed: R1.2, U$1.7 (PRGM), U$3.7
unnamed: R1.1, U$1.8 (REF), U$3.8
unnamed: U$1.6 (ENABLE), U$3.10
unnamed: U$1.3 (OUTPUT+), U$2.2, U$2.3, U$2.4
unnamed: U$1.5 (C.TAP), U$2.5, U$2.6, U$2.7
unnamed: R2.2, R3.2, U$1.1 (INPUT+)
unnamed: R4.1, R10.2, U1.2 (1IN-)
unnamed: C9.1, R8.1
unnamed: SV1.7, SV1.8
unnamed: D4.A, R11.2, R12.1
unnamed: D1.A, R13.2, R14.1
unnamed: D2.A, R15.2, R16.1
unnamed: D3.A, R17.2, R18.1
unnamed: POT.2 (S), POT.3 (E), R5.1, U1.1 (1OUT)
unnamed: PIN.1, R5.2, R6.2
unnamed: PIN.9, PIN.10, R7.1
unnamed: PIN.4, R8.2
unnamed: PIN.6, R6.1, R7.2, S17.1, S18.1
unnamed: R10.1, S1.1, S19.2
unnamed: POT.1 (A), R4.2
unnamed: C9.2, PIN.5
V+: C1.1, C2.1, PIN.11, PIN.12, R13.1, SV2.7, SV2.8, SV2.9

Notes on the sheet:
PSU

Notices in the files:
parts and their libraries:
SparkFun-Capacitors: Licensing: Creative Commons ShareAlike 4.0 International - https://creativecommons.org/licenses/by-sa/4.0
